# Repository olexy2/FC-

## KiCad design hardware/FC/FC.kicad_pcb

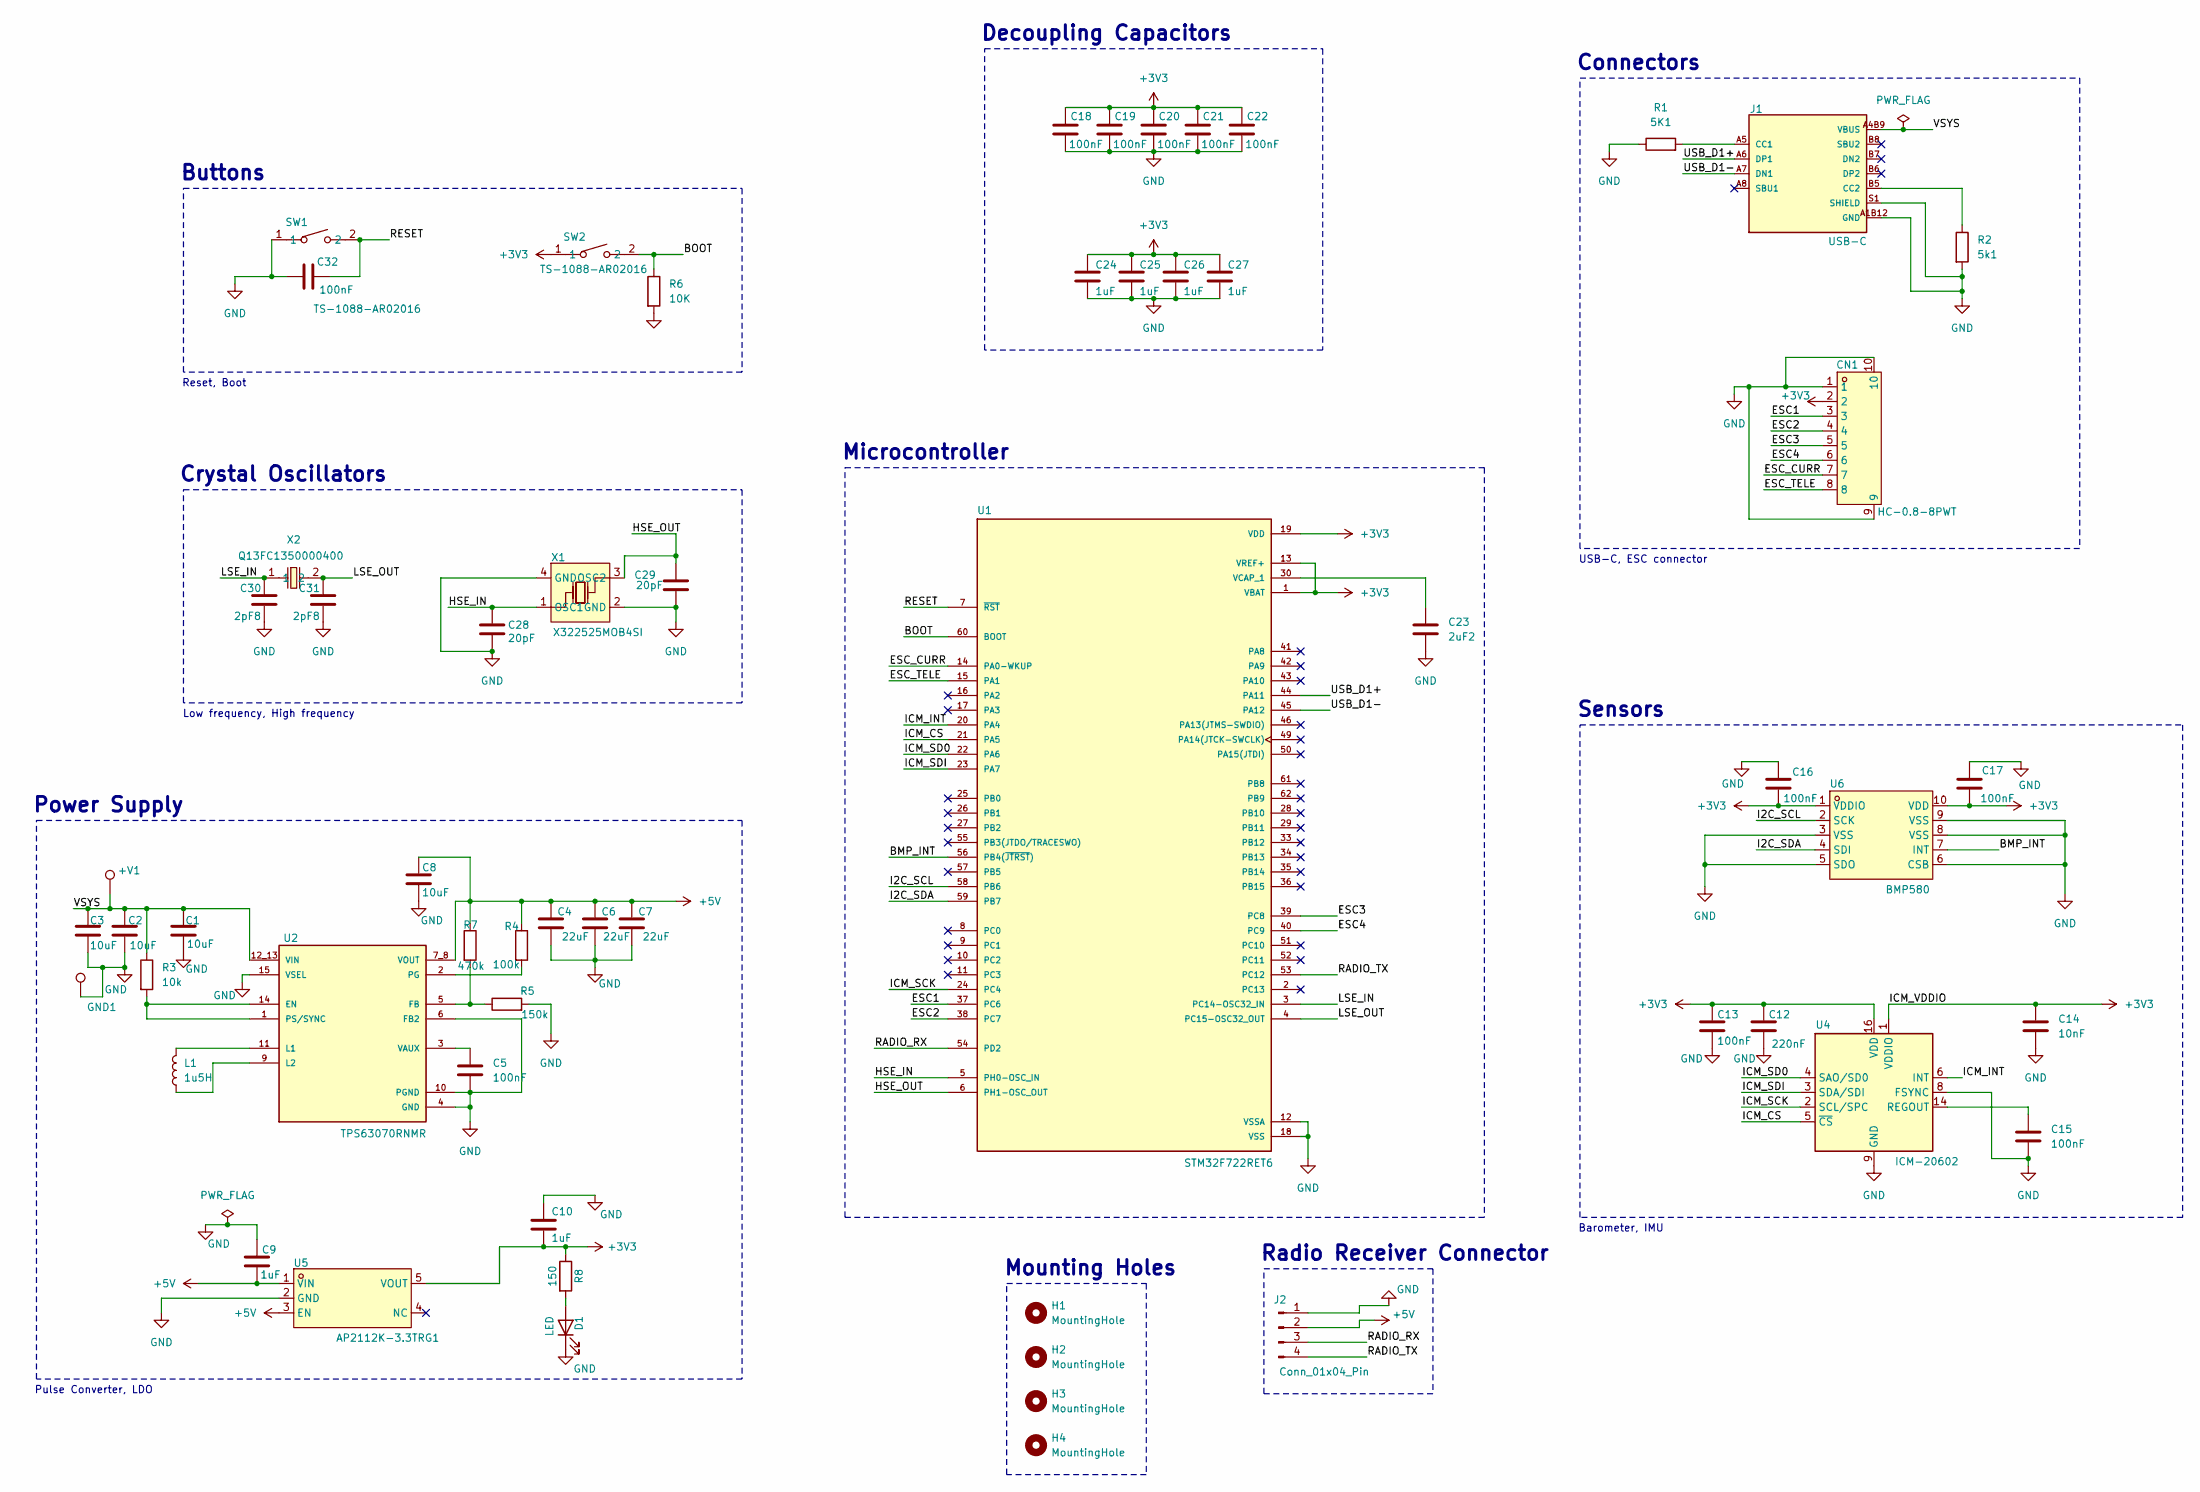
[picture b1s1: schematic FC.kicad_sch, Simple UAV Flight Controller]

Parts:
+V1: TestPoint_Pad_4.0x4.0mm
C1, C2, C3, C8: 10uF; C_0805_2012Metric
C4, C6, C7: 22uF; C_1206_3216Metric
C5: 100nF; C_0805_2012Metric
C9, C10, C24, C25, C26, C27: 1uF; C_0805_2012Metric
C12: 220nF; C_0603_1608Metric
C13, C15, C16, C17, C18, C19, C20, C21, C22, C32: 100nF; C_0603_1608Metric
C14: 10nF; C_0402_1005Metric
C23: 2uF2; C_0805_2012Metric
C28, C29: 20pF; C_0402_1005Metric
C30, C31: 2pF8; C_0402_1005Metric
CN1: HC-0.8-8PWT; CONN-SMD_8P-P0.80_HCTL_HC-0.8-8PWT; MPN HC-0.8-8PWT; LCSC Part C2845349
D1: LED; D_0805_2012Metric_Pad1.15x1.40mm_HandSolder
GND1: TestPoint_Pad_4.0x4.0mm
H1, H2, H3, H4: MountingHole; MountingHole_2.2mm_M2
J1: USB-C; HRO_TYPE-C-31-M-12; LCSCPART# C165948
J2: Conn_01x04_Pin; radio_solder_pads
L1: 1u5H; L_0603_1608Metric
R1: 5K1; R_0201_0603Metric
R2: 5k1; R_0201_0603Metric
R3: 10k; R_0201_0603Metric
R4: 100k; R_0201_0603Metric
R5: 150k; R_0201_0603Metric
R6: 10K; R_0201_0603Metric
R7: 470k; R_0201_0603Metric
R8: 150; R_0603_1608Metric_Pad0.98x0.95mm_HandSolder
SW1, SW2: TS-1088-AR02016; SW-SMD_L3.9-W3.0-P4.45; MPN TS-1088-AR02016; LCSC Part C720477
U1: STM32F722RET6; QFP50P1200X1200X160-64N; PARTREV 4
U2: TPS63070RNMR; VREG_TPS63070RNMR; PARTREV B
U4: ICM-20602; LGA-16_3x3mm_P0.5mm_LayoutBorder3x5y
U5: AP2112K-3.3TRG1; AP2112K-3.3; MPN AP2112K-3.3TRG1; LCSC Part C51118
U6: BMP580; LGA-10_L2.0-W2.0-P0.50-TL_BMP580; MPN BMP580; LCSC Part C22391138
X1: X322525MOB4SI; CRYSTAL-SMD_4P-L3.2-W2.5-BL; MPN X322525MOB4SI; LCSC Part C9006
X2: Q13FC1350000400; FC-135R_L3.2-W1.5; MPN Q13FC13500004; LCSC Part C32346

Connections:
+3V3: C10.2, C12.2, C13.2, C14.1, C16.2, C17.2, C18.1, C19.1, C20.1, C21.1, C22.1, C24.1, C25.1, C26.1, C27.1, CN1.2, R8.1, SW2.1, U1.1 (VBAT), U1.13 (VREF+), U1.19 (VDD), U1.32 (VDD), U1.48 (VDD), U1.64 (VDD), U4.1 (VDDIO), U4.16 (VDD), U5.5 (VOUT), U6.1 (VDDIO), U6.10 (VDD)
+5V: C4.1, C6.1, C7.1, C8.1, C9.2, J2.2, R4.1, R7.1, U2.7_8 (VOUT), U5.1 (VIN), U5.3 (EN)
/BMP_INT: U1.56 (PB4(~JTRST)), U6.7 (INT)
/BOOT: R6.1, SW2.2, U1.60 (BOOT)
/ESC1: CN1.3, U1.37 (PC6)
/ESC2: CN1.4, U1.38 (PC7)
/ESC3: CN1.5, U1.39 (PC8)
/ESC4: CN1.6, U1.40 (PC9)
/ESC_CURR: CN1.7, U1.14 (PA0-WKUP)
/ESC_TELE: CN1.8, U1.15 (PA1)
/HSE_IN: C28.2, U1.5 (PH0-OSC_IN), X1.1 (OSC1)
/HSE_OUT: C29.2, U1.6 (PH1-OSC_OUT), X1.3 (OSC2)
/I2C_SCL: U1.58 (PB6), U6.2 (SCK)
/I2C_SDA: U1.59 (PB7), U6.4 (SDI)
/ICM_CS: U1.21 (PA5), U4.5 (~CS)
/ICM_INT: U1.20 (PA4), U4.6 (INT)
/ICM_SCK: U1.24 (PC4), U4.2 (SCL/SPC)
/ICM_SD0: U1.22 (PA6), U4.4 (SAO/SD0)
/ICM_SDI: U1.23 (PA7), U4.3 (SDA/SDI)
/LSE_IN: C30.1, U1.3 (PC14-OSC32_IN), X2.1
/LSE_OUT: C31.1, U1.4 (PC15-OSC32_OUT), X2.2
/RADIO_RX: J2.3, U1.54 (PD2)
/RADIO_TX: J2.4, U1.53 (PC12)
/RESET: C32.2, SW1.2, U1.7 (~RST)
/USB_D1+: J1.A6 (DP1), U1.44 (PA11)
/USB_D1-: J1.A7 (DN1), U1.45 (PA12)
GND: C1.2, C2.2, C3.2, C4.2, C5.2, C6.2, C7.2, C8.2, C9.1, C10.1, C12.1, C13.1, C14.2, C15.2, C16.1, C17.1, C18.2, C19.2, C20.2, C21.2, C22.2, C23.2, C24.2, C25.2, C26.2, C27.2, C28.1, C29.1, C30.2, C31.2, C32.1, CN1.1, CN1.9, CN1.10, D1.1 (K), GND1.1 (1_1), J1.A1B12 (GND), J1.B1A12 (GND), J1.S1 (SHIELD), J1.S2 (SHIELD), J1.S3 (SHIELD), J1.S4 (SHIELD), J2.1, R1.1, R2.2, R5.2, R6.2, SW1.1, U1.12 (VSSA), U1.18 (VSS), U1.31 (VSS), U1.47 (VSS), U1.63 (VSS), U2.4 (GND), U2.6 (FB2), U2.10 (PGND), U2.15 (VSEL), U4.8 (FSYNC), U4.9 (GND), U4.10 (GND), U4.11 (GND), U4.12 (GND), U4.13 (GND), U4.15 (GND), U5.2 (GND), U6.3 (VSS), U6.5 (SDO), U6.6 (CSB), U6.8 (VSS), U6.9 (VSS), X1.2 (GND), X1.4 (GND)
unnamed: D1.2 (A), R8.2
unnamed: J1.A5 (CC1), R1.2
unnamed: J1.B5 (CC2), R2.1
unnamed: C23.1, U1.30 (VCAP_1)
unnamed: R3.2, U2.1 (PS/SYNC), U2.14 (EN)
unnamed: R5.1, R7.2, U2.5 (FB)
unnamed: L1.2, U2.11 (L1)
unnamed: L1.1, U2.9 (L2)
unnamed: R4.2, U2.2 (PG)
unnamed: C5.1, U2.3 (VAUX)
unnamed: C15.1, U4.14 (REGOUT)
VBUS: +V1.1 (1_1), C1.1, C2.1, C3.1, J1.A4B9 (VBUS), J1.B4A9 (VBUS), R3.1, U2.12_13 (VIN)

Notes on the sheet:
Crystal Oscillators
Microcontroller
Sensors
Radio Receiver Connector
Reset, Boot
Power Supply
Low frequency, High frequency
Mounting Holes
Buttons
Pulse Converter, LDO
Barometer, IMU
Decoupling Capacitors
Connectors
USB-C, ESC connector

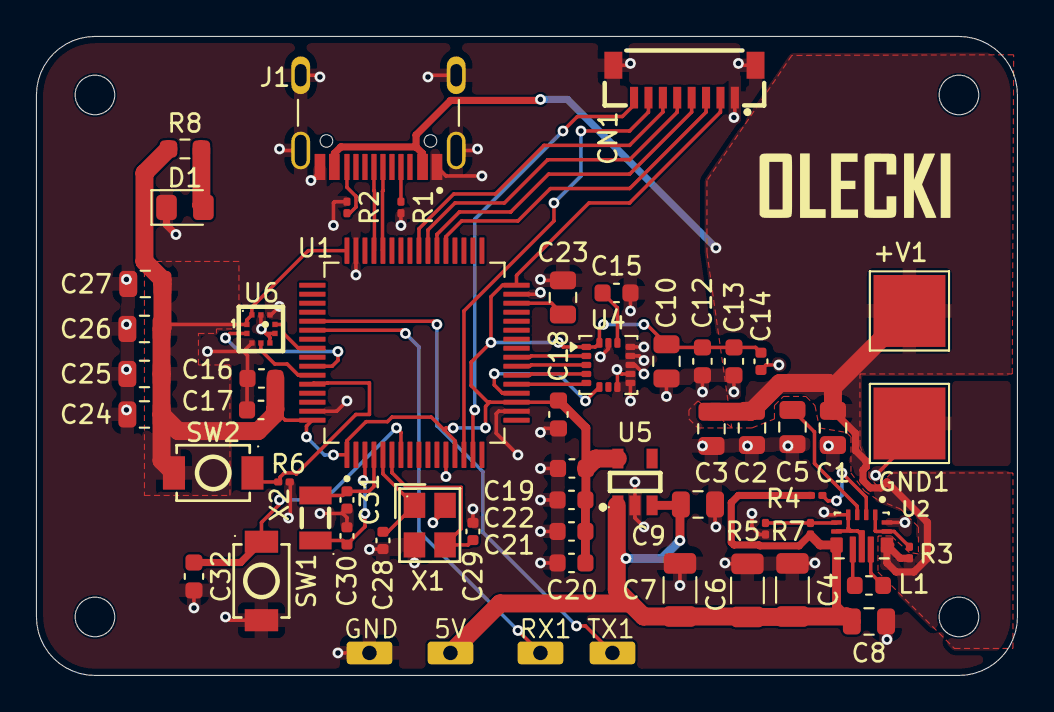
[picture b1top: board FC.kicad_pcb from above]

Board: 2 copper layers, 54.5 x 35.5 mm, 58 parts (0 on the bottom side), 37 nets.

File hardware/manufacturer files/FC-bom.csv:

"Reference","Qty","Value","Footprint","Datasheet"
"+V1,GND1","2","","TestPoint:TestPoint_Pad_4.0x4.0mm",""
"C1,C2,C3,C8","4","10uF","Capacitor_SMD:C_0805_2012Metric",""
"C4,C6,C7","3","22uF","Capacitor_SMD:C_1206_3216Metric",""
"C5","1","100nF","Capacitor_SMD:C_0805_2012Metric",""
"C9,C10,C24,C25,C26,C27","6","1uF","Capacitor_SMD:C_0805_2012Metric",""
"C12","1","220nF","Capacitor_SMD:C_0603_1608Metric",""
"C13,C15,C16,C17,C18,C19,C20,C21,C22,C32","10","100nF","Capacitor_SMD:C_0603_1608Metric",""
"C14","1","10nF","Capacitor_SMD:C_0402_1005Metric",""
"C23","1","2uF2","Capacitor_SMD:C_0805_2012Metric",""
"C28,C29","2","20pF","Capacitor_SMD:C_0402_1005Metric",""
"C30,C31","2","2pF8","Capacitor_SMD:C_0402_1005Metric",""
"CN1","1","HC-0.8-8PWT","CONNECTOR 8-PIN:CONN-SMD_8P-P0.80_HCTL_HC-0.8-8PWT","https://www.lcsc.com/datasheet/C2845349.pdf"
"D1","1","LED","Diode_SMD:D_0805_2012Metric_Pad1.15x1.40mm_HandSolder",""
"J1","1","USB-C","USB-C:HRO_TYPE-C-31-M-12",""
"J2","1","Conn_01x04_Pin","RADIO_SOLDER_PADS:radio_solder_pads",""
"L1","1","1u5H","Inductor_SMD:L_0603_1608Metric",""
"R1","1","5K1","Resistor_SMD:R_0201_0603Metric",""
"R2","1","5k1","Resistor_SMD:R_0201_0603Metric",""
"R3","1","10k","Resistor_SMD:R_0201_0603Metric",""
"R4","1","100k","Resistor_SMD:R_0201_0603Metric",""
"R5","1","150k","Resistor_SMD:R_0201_0603Metric",""
"R6","1","10K","Resistor_SMD:R_0201_0603Metric",""
"R7","1","470k","Resistor_SMD:R_0201_0603Metric",""
"R8","1","150","Resistor_SMD:R_0603_1608Metric_Pad0.98x0.95mm_HandSolder",""
"SW1,SW2","2","TS-1088-AR02016","RST_BTN:SW-SMD_L3.9-W3.0-P4.45","https://lcsc.com/product-detail/Tactile-Switches_XUNPU-TS-10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"
"U1","1","STM32F722RET6","STM32F722RET6:QFP50P1200X1200X160-64N",""
"U2","1","TPS63070RNMR","TPS63070RNMR:VREG_TPS63070RNMR",""
"U4","1","ICM-20602","Package_LGA:LGA-16_3x3mm_P0.5mm_LayoutBorder3x5y","http://www.invensense.com/wp-content/uploads/2016/10/DS-0001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"
"U5","1","AP2112K-3.3TRG1","AP2112K-3.3:AP2112K-3.3","https://lcsc.com/product-detail/Low-Dropout-Regulators-LDO_D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"
"U6","1","BMP580","BMP580:LGA-10_L2.0-W2.0-P0.50-TL_BMP580","https://www.lcsc.com/datasheet/C22391138.pdf"
"X1","1","X322525MOB4SI","25MHz_CRYSTAL:CRYSTAL-SMD_4P-L3.2-W2.5-BL","https://lcsc.com/product-detail/SMD-Crystals_YSX321SL-25MHZ-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"
"X2","1","Q13FC1350000400","32.768kHz_CRYSTAL:FC-135R_L3.2-W1.5","https://lcsc.com/product-detail/SMD-Crystals_EPSON_Q13FC1350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"

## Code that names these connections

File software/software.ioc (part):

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Mcu.Name=STM32F722R(C-E)Tx
Mcu.Package=LQFP64
Mcu.UserName=STM32F722RETx
PA0-WKUP.GPIOParameters=GPIO_Label
PA0-WKUP.GPIO_Label=ESC_CURR
PA0-WKUP.Signal=ADCx_IN0
PA1.Mode=Asynchronous
PA1.Signal=UART4_RX
PA11.GPIOParameters=GPIO_Label
PA11.GPIO_Label=USB_D1-
PA11.Mode=Host_Only
PA11.Signal=USB_OTG_FS_DM
PA12.GPIOParameters=GPIO_Label
PA12.GPIO_Label=USB_D1+
PA12.Mode=Host_Only
PA12.Signal=USB_OTG_FS_DP
PA4.GPIOParameters=GPIO_Label
PA4.GPIO_Label=ICM_INT
PA4.Mode=NSS_Signal_Hard_Output
PA4.Signal=SPI1_NSS
PA5.GPIOParameters=GPIO_Label
PA5.GPIO_Label=ICM_CS
PA5.Mode=Full_Duplex_Master
PA5.Signal=SPI1_SCK
PA6.GPIOParameters=GPIO_Label
PA6.GPIO_Label=ICM_SD0
PA6.Mode=Full_Duplex_Master
PA6.Signal=SPI1_MISO
PA7.GPIOParameters=GPIO_Label
PA7.GPIO_Label=ICM_SDI
PA7.Mode=Full_Duplex_Master
PA7.Signal=SPI1_MOSI
PB6.GPIOParameters=GPIO_Label
PB6.GPIO_Label=I2C_SCL
PB6.Mode=I2C
PB6.Signal=I2C1_SCL
PB7.GPIOParameters=GPIO_Label
PB7.GPIO_Label=I2C_SDA
PB7.Mode=I2C
PB7.Signal=I2C1_SDA
PC10.GPIOParameters=GPIO_Label
PC10.GPIO_Label=ESC_TELE
PC10.Mode=Asynchronous
PC10.Signal=UART4_TX
PC12.GPIOParameters=GPIO_Label
PC12.GPIO_Label=RADIO_TX
PC12.Mode=Asynchronous
PC12.Signal=UART5_TX
PC14-OSC32_IN.GPIOParameters=GPIO_Label
PC14-OSC32_IN.GPIO_Label=LSE_IN
PC14-OSC32_IN.Mode=LSE-External-Oscillator
PC14-OSC32_IN.Signal=RCC_OSC32_IN
PC15-OSC32_OUT.GPIOParameters=GPIO_Label
PC15-OSC32_OUT.GPIO_Label=LSE_OUT
PC15-OSC32_OUT.Mode=LSE-External-Oscillator
PC15-OSC32_OUT.Signal=RCC_OSC32_OUT
PC4.GPIOParameters=GPIO_Label
PC4.GPIO_Label=ICM_SCK
PC4.Signal=GPXTI4
PC6.GPIOParameters=GPIO_Label
PC6.GPIO_Label=ESC1
PC6.Signal=S_TIM8_CH1
PC7.GPIOParameters=GPIO_Label
PC7.GPIO_Label=ESC2
PC7.Signal=S_TIM8_CH2
PC8.GPIOParameters=GPIO_Label
PC8.GPIO_Label=ESC3
PC8.Signal=S_TIM8_CH3
PC9.GPIOParameters=GPIO_Label
PC9.GPIO_Label=ESC4
PC9.Signal=S_TIM8_CH4
PD2.GPIOParameters=GPIO_Label
PD2.GPIO_Label=RADIO_RX
PD2.Mode=Asynchronous
PD2.Signal=UART5_RX
PH0-OSC_IN.GPIOParameters=GPIO_Label
PH0-OSC_IN.GPIO_Label=HSE_IN
PH0-OSC_IN.Mode=HSE-External-Oscillator
PH0-OSC_IN.Signal=RCC_OSC_IN
PH1-OSC_OUT.GPIOParameters=GPIO_Label
PH1-OSC_OUT.GPIO_Label=HSE_OUT
PH1-OSC_OUT.Mode=HSE-External-Oscillator
PH1-OSC_OUT.Signal=RCC_OSC_OUT
RCC.HSE_VALUE=25000000
board=custom

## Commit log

2026-05-09 Pierwszy commit
2026-05-09 fixed kicad files
2026-05-10 added bmp580
2026-05-11 added LDO and all components on scheme
2026-05-12 added ESC pinout
2026-06-04 added software.ioc
2026-06-04 added lib files
2026-06-04 sucsessful ERC, started PCB layout
2026-06-08 added pcb design
2026-06-14 added LED for PS
2026-06-19 fixed vbus line, added diode and graphic
